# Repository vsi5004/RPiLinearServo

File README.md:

# RPiLinearServo

A closed-loop linear servo based on the RP2040, using a micro stepper linear actuator with an 8.5 mm throw and a BTT v1.3 TMC2209 driver. Designed as an RC servo replacement / turnout actuator for model railroads that allows for smooth and reliable slow speed operation and ease of configuration for a wide range of applications.

## Features

- Controllable via standard servo PWM signal allowing for plug-and-play integration in systems designed for miniature R/C servos
- Easy firmware updates - just drag and drop compiled binary into mounted drive to flash
- Widely configurable by editing a `CONFIG.INI` file when device is connected as a usb drive to allow for adaptation to wide range of use cases
- Smooth, quiet, controllable, and repeatable motion not available in smaller servos
- Non-backdrivable lead screw linear stage can be powered off in a low power state while not in use
- Automatic homing routine runs once and is then stored and persists throughout the life of the device
- Closed loop magnetic feedback allows for seamless, accurate adjustments if external factors cause motor to miss steps
- Interactive USB CLI (via serial monitor) exposes full command set for motion control, diagnostics, and debugging

## Hardware

| Component | Details |
|---|---|
| MCU | Waveshare RP2040-Zero |
| Driver | BTT TMC2209 v1.3 SilentStepStick |
| Actuator | Micro stepper linear slide, 8.4 mm travel (~208.3 full steps/mm) |
| Hall Sensor | TI DRV5055 A2 (optional, for closed-loop verification) |

See the [PCB README](PCB/README.md) for the full schematic, BOM, and GPIO assignments.

## Getting Started

### Flash the firmware

1. Hold **BOOTSEL** on the RP2040-Zero and plug in USB.
2. Drag `RPiLinearServo.uf2` onto the **RPI-RP2** drive.
3. The board reboots and enumerates as a composite USB device (CDC serial + MSC config drive).

Pre-built `.uf2` files are available on the [Releases](../../releases) page — or build from source (see the [Firmware README](Firmware/RPiLinearServo/README.md)).

### Connect a PWM signal

Wire a standard RC servo signal (1000–2000 µs) to GP0. On the first valid pulse the servo automatically homes (drives into the hardstop, backs off, and zeroes) then begins tracking the PWM target.

If the PWM signal is lost for more than 100 ms (configurable), the motor is disabled and the LED enters an idle heartbeat.

### Configure via USB drive

The device mounts a small USB drive named **LINEARSERVO** containing `CONFIG.INI`. Edit with any text editor, save, and **safely eject**. The firmware applies changes within ~500 ms.

```ini
[stroke]
stroke_mm = 8.40
full_steps_per_mm = 208.3

[driver]
dir_invert = false
run_current_ma = 100
hold_current_ma = 50

[motion]
default_speed_mm_s = 40.0
max_accel_mm_s2 = 80.0
auto_disable_ms = 2000

[rc_pwm]
min_us = 1000
max_us = 2000

[led]
dark_mode = false

[power]
sleep_when_idle = false

[sensor]
use_hall_effect = false
```

### USB CLI

Connect a serial terminal (PuTTY, minicom, `screen /dev/ttyACM0 115200`) to the CDC port. The CLI is always active alongside PWM control.

```
> help
Commands:
  move <steps> [speed_hz]  Move relative steps (negative = reverse)
  run [speed_hz]           Continuous stepping
  stop                     Stop immediately
  home                     Run homing sequence
  enable                   Enable motor driver
  disable                  Disable motor driver
  dir <fwd|rev>            Set direction for 'run'
  speed <hz>               Set default speed
  pos                      Print position
  status                   Print full status
  pwm                      Print PWM input status
  nvm                      Print/save position state
  hall                     Hall sensor reading
  hallcal                  Dump hall calibration table
  faultclr                 Clear stall fault
  help                     This message
```

CLI commands go through the same servo loop state machine as PWM-driven moves, so LED and driver enable behaviour is always consistent.

## Project Structure

| Directory | Description | Details |
|---|---|---|
| [Firmware/RPiLinearServo](Firmware/RPiLinearServo/README.md) | RP2040 firmware (C++17, Pico SDK) | Build instructions, architecture, module reference |
| [PCB](PCB/README.md) | KiCad 8 schematic & PCB | BOM, GPIO map, sourcing notes, Gerber outputs |
| [Mechanical](Mechanical/README.md) | 3D-printable mounting hardware | Mount variants, print settings, additional parts |
| [Docs](Docs/) | Renders and specifications | Project renders, design spec |

## License

This project is licensed under the [MIT License](LICENSE).

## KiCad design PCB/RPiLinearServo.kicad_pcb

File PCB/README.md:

# PCB — RPiLinearServo

KiCad schematic and PCB design files for the RPiLinearServo controller board.

## GPIO Assignments

| Signal | RP2040-Zero | TMC2209 Pin | Notes |
|---|---|---|---|
| PWM input | GP0 | — | RC servo signal via PIO1/SM1 |
| nENABLE | GP1 | EN | Active-low driver enable |
| STEP | GP2 | STEP | PIO0/SM0 driven |
| DIR | GP3 | DIR | GPIO |
| UART TX | GP4 | PDN/UART | Via 1 kΩ series resistor on PCB |
| UART RX | GP5 | PDN/UART | Loopback on bus |
| INDEX | GP7 | INDEX | Unused (reserved) |
| DIAG | GP9 | DIAG | Unused (reserved) |
| LED | GP16 | — | WS2812 RGB via PIO1/SM0 |
| Hall sensor | GP26 | — | DRV5055 A2 analog via ADC0 |

### UART bus isolation

The 1 kΩ series resistor (R1) between GP4 and the TMC2209 PDN/UART pin provides signal isolation so the driver can pull the bus low during reply frames without fighting the RP2040 TX output. GP4 is tri-stated after each write to allow the TMC2209 to respond over the half-duplex bus.

### PWM input protection

The PWM input on GP0 is routed through a 74LVC1G17 Schmitt-trigger buffer (U4) for signal conditioning. A TPD1E10B06DPYR ESD protection diode (D1) clamps the input to protect against transient voltage spikes from the RC servo signal line.

## Bill of Materials

| Ref | Part | Value / Description | Package | Qty |
|---|---|---|---|---|
| U2 | Waveshare RP2040-Zero | Dual-core RP2040 MCU module | Through-hole module | 1 |
| U1 | BTT TMC2209 v1.3 SilentStepStick | Stepper driver with UART | Through-hole module | 1 |
| U3 | TI DRV5055A2xDBZxQ1 | Ratiometric linear hall-effect sensor, 25 mV/mT | SOT-23 | 1 |
| U4 | 74LVC1G17 | Single Schmitt-trigger buffer | SOT-23-5 | 1 |
| D1 | TI TPD1E10B06DPYR | ESD protection diode, ±30 kV HBM | 0402 | 1 |
| C1, C3 | Panasonic EEEFPC101XAP | 100 µF 16 V aluminum electrolytic | Radial (custom footprint) | 2 |
| C2, C5 | Ceramic | 2.2 µF | 0805 | 2 |
| C4, C6 | Ceramic | 0.1 µF (decoupling) | 0402 | 2 |
| R1, R2 | Resistor | 1 kΩ | 0603 | 2 |
| R3 | Resistor | 330 Ω | 0603 | 1 |
| J1 | Pin header 1×3 | Hall sensor / PWM input connector | 2.54 mm pitch | 1 |
| J2 | Pin header 2×2 (omit, used for pads only)| Stepper motor phase connector | 2.54 mm pitch | 1 |

### Sourcing notes

| Part | Suggested source |
|---|---|
| Waveshare RP2040-Zero | [Waveshare](https://www.waveshare.com/rp2040-zero.htm), AliExpress, Amazon |
| BTT TMC2209 v1.3 SilentStepStick | [BIGTREETECH](https://biqu.equipment/products/bigtreetech-tmc2209-stepper-motor-driver-for-3d-printer-board-vs-tmc2208), Amazon, AliExpress |
| TI DRV5055A2xDBZxQ1 | DigiKey, Mouser, LCSC |
| 74LVC1G17 | DigiKey, Mouser, LCSC |
| TPD1E10B06DPYR | DigiKey (296-30406-1-ND), Mouser |
| Panasonic EEEFPC101XAP | DigiKey (PCE4534CT-ND), Mouser |
| Passives (0402/0603/0805) | LCSC, DigiKey, Mouser |

All SMD passives use hand-solder footprints with extended pads for easier assembly.

## Design Files

| Path | Description |
|---|---|
| `RPiLinearServo.kicad_sch` | Schematic |
| `RPiLinearServo.kicad_pcb` | PCB layout |
| `RPiLinearServo.kicad_pro` | KiCad project |
| `RPiLinearServo.step` | 3D model of assembled board |
| `Components/` | Custom KiCad symbol libraries + 3D STEP models |
| `CustomFootprints/` | Custom KiCad footprint libraries |

## Manufacturing Outputs

Pre-generated Gerber and drill files are in `Outputs/`:

| File | Description |
|---|---|
| `*-F_Cu.gbr`, `*-B_Cu.gbr` | Front/back copper |
| `*-F_Mask.gbr`, `*-B_Mask.gbr` | Front/back solder mask |
| `*-F_Paste.gbr`, `*-B_Paste.gbr` | Front/back paste stencil |
| `*-F_Silkscreen.gbr`, `*-B_Silkscreen.gbr` | Front/back silkscreen |
| `*-Edge_Cuts.gbr` | Board outline |
| `*-PTH.drl`, `*-NPTH.drl` | Plated / non-plated drill files |
| `*-top-pos.csv`, `*-bottom-pos.csv` | Pick-and-place position files |
| `*-BOM.csv` | Bill of materials (semicolon-delimited) |
| `*-job.gbrjob` | Gerber job file |

These files are ready to upload directly to PCB fabricators such as JLCPCB, PCBWay, or OSH Park.

### PCB specifications

| Parameter | Value |
|---|---|
| Minimum trace width | 0.2 mm |
| Default trace width | 0.2 mm |
| Via diameter / drill | 0.6 mm / 0.3 mm |
| Copper-to-edge clearance | 0.4 mm |
| Layers | 2 |

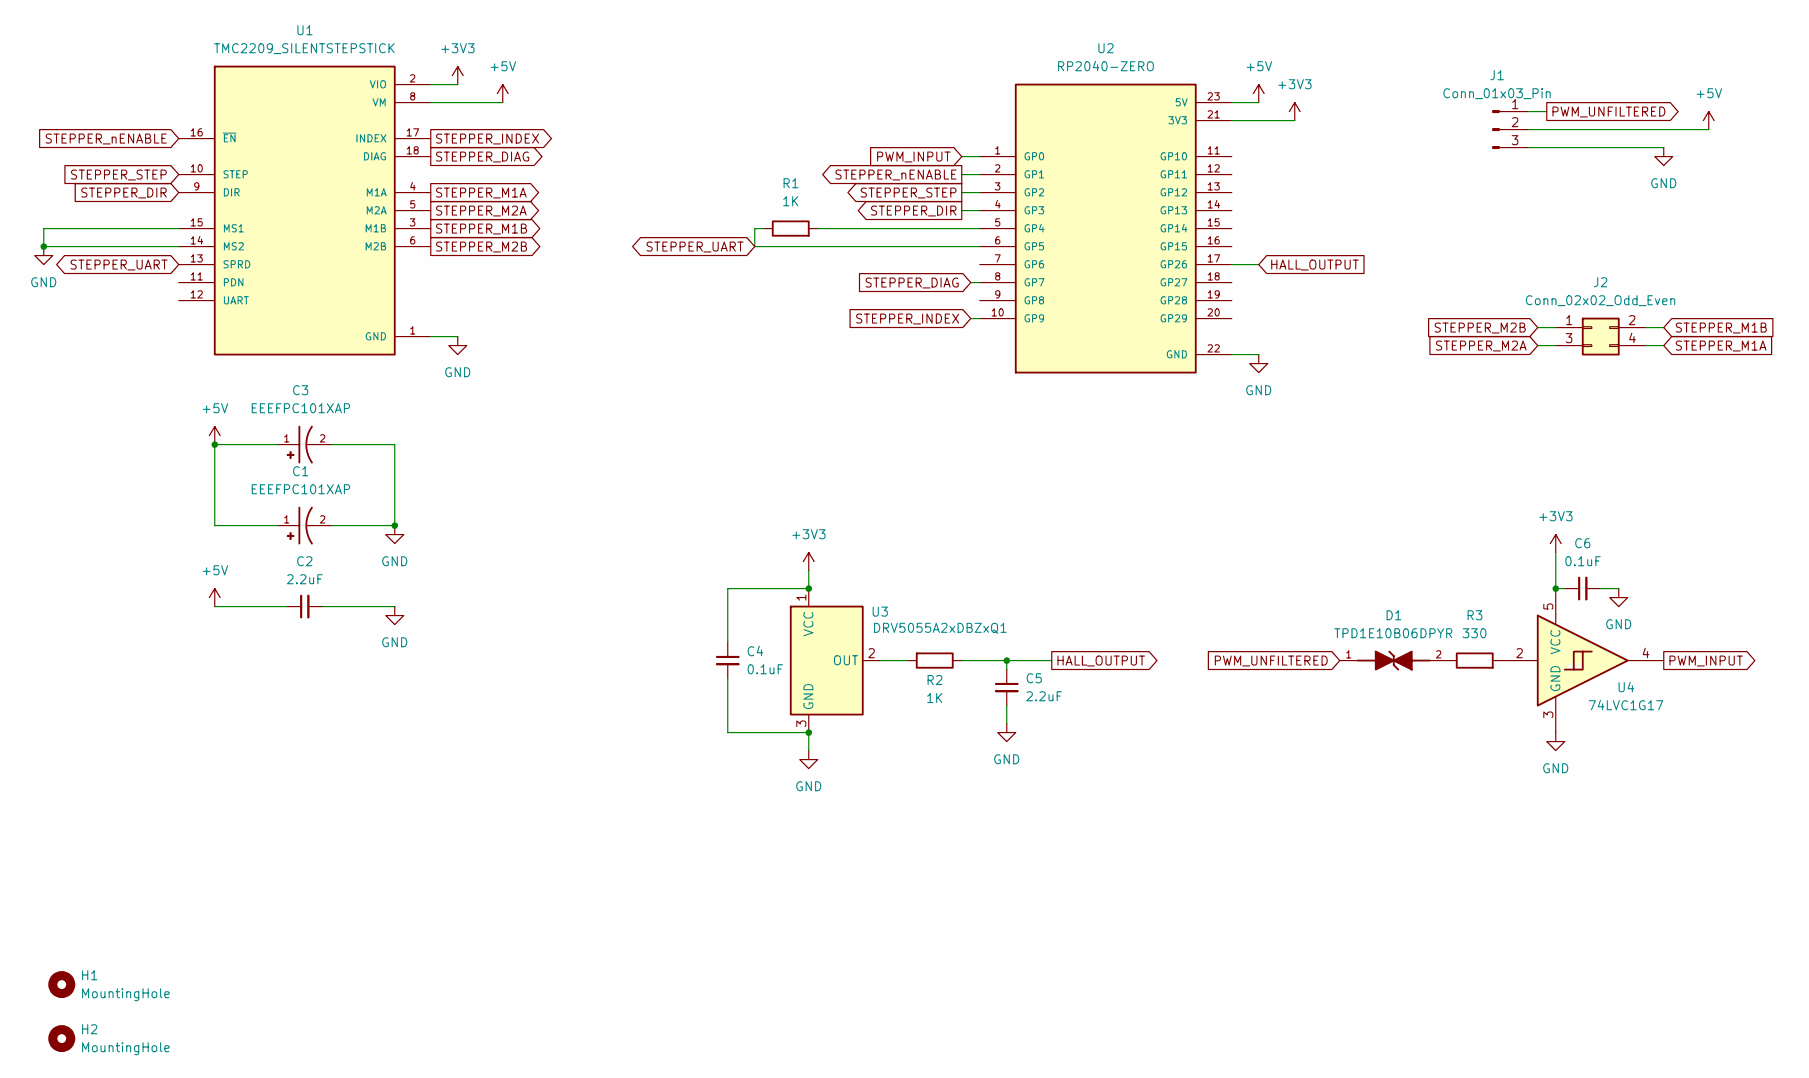
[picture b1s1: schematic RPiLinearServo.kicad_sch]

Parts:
C1, C3: EEEFPC101XAP; CAP_EEEFPC101XAP; PARTREV 10-Oct-19; DigiKey_Part_Number PCE4534CT-ND
C2, C5: 2.2uF; C_0805_2012Metric_Pad1.18x1.45mm_HandSolder
C4, C6: 0.1uF; C_0402_1005Metric_Pad0.74x0.62mm_HandSolder
D1: TPD1E10B06DPYR; D_0402_1005Metric_Pad0.77x0.64mm_HandSolder; PARTREV G; DigiKey_Part_Number 296-30406-1-ND
H1, H2: MountingHole; MountingHole_2.2mm_M2_DIN965_Pad
J1: Conn_01x03_Pin; PinHeader_1x03_P2.54mm_Vertical
J2: Conn_02x02_Odd_Even; PinHeader_2x02_P2.54mm_Vertical
R1, R2: 1K; R_0603_1608Metric_Pad0.98x0.95mm_HandSolder
R3: 330; R_0603_1608Metric_Pad0.98x0.95mm_HandSolder
U1: TMC2209_SILENTSTEPSTICK; MODULE_TMC2209_SILENTSTEPSTICK
U2: RP2040-ZERO; MODULE_RP2040-ZERO; PARTREV NA
U3: DRV5055A2xDBZxQ1; SOT-23_Handsoldering
U4: 74LVC1G17; SOT-23-5_HandSoldering

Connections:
+3V3: C4.1, C6.1, U1.2 (VIO), U2.21 (3V3), U3.1 (VCC), U4.5 (VCC)
+5V: C1.1, C2.1, C3.1, J1.2, U1.8 (VM), U2.23 (5V)
GND: C1.2, C2.2, C3.2, C4.2, C5.2, C6.2, J1.3, U1.1 (GND), U1.7 (GND), U1.14 (MS2), U1.15 (MS1), U2.22 (GND), U3.3 (GND), U4.3 (GND)
HALL_OUTPUT: C5.1, R2.1, U2.17 (GP26)
unnamed: D1.2, R3.1
unnamed: R3.2, U4.2
unnamed: R1.2, U2.5 (GP4)
unnamed: R2.2, U3.2 (OUT)
PWM_INPUT: U2.1 (GP0), U4.4
PWM_UNFILTERED: D1.1, J1.1
STEPPER_DIAG: U1.18 (DIAG), U2.8 (GP7)
STEPPER_DIR: U1.9 (DIR), U2.4 (GP3)
STEPPER_INDEX: U1.17 (INDEX), U2.10 (GP9)
STEPPER_M1A: J2.4, U1.4 (M1A)
STEPPER_M1B: J2.2, U1.3 (M1B)
STEPPER_M2A: J2.3, U1.5 (M2A)
STEPPER_M2B: J2.1, U1.6 (M2B)
STEPPER_STEP: U1.10 (STEP), U2.3 (GP2)
STEPPER_UART: R1.1, U1.13 (SPRD), U2.6 (GP5)
STEPPER_nENABLE: U1.16 (~EN), U2.2 (GP1)

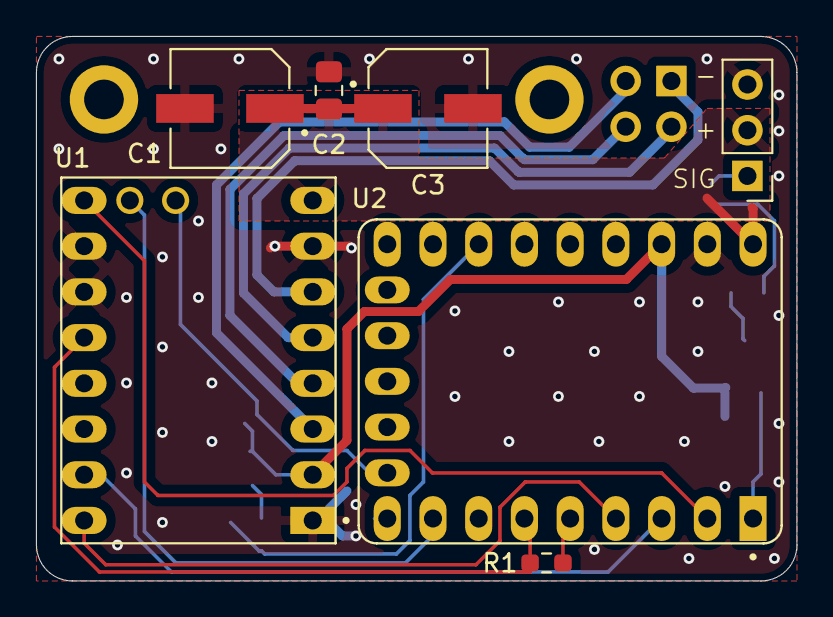
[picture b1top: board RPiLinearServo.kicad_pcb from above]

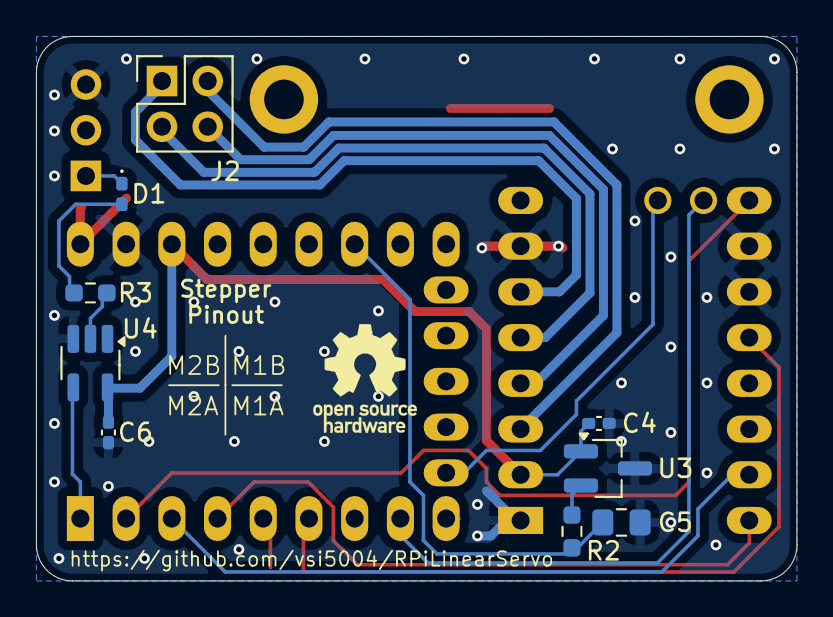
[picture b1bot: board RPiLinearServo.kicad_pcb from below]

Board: 2 copper layers, 42.2 x 30.2 mm, 18 parts (9 on the bottom side), 20 nets.

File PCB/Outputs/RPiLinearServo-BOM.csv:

"Id";"Designator";"Footprint";"Quantity";"Designation";"Supplier and ref";
1;"C1,C3";"CAP_EEEFPC101XAP";2;"EEEFPC101XAP";;;
2;"J1";"PinHeader_1x03_P2.54mm_Vertical";1;"Conn_01x03_Pin";;;
3;"U2";"MODULE_RP2040-ZERO";1;"RP2040-ZERO";;;
4;"R1,R2";"R_0603_1608Metric_Pad0.98x0.95mm_HandSolder";2;"1K";;;
5;"U1";"MODULE_TMC2209_SILENTSTEPSTICK";1;"TMC2209_SILENTSTEPSTICK";;;
6;"C2,C5";"C_0805_2012Metric_Pad1.18x1.45mm_HandSolder";2;"2.2uF";;;
7;"J2";"PinHeader_2x02_P2.54mm_Vertical";1;"Conn_02x02_Odd_Even";;;
8;"D1";"D_0402_1005Metric_Pad0.77x0.64mm_HandSolder";1;"TPD1E10B06DPYR";;;
9;"C4,C6";"C_0402_1005Metric_Pad0.74x0.62mm_HandSolder";2;"0.1uF";;;
10;"U4";"SOT-23-5_HandSoldering";1;"74LVC1G17";;;
11;"U3";"SOT-23_Handsoldering";1;"DRV5055A3xDBZxQ1";;;
12;"R3";"R_0603_1608Metric_Pad0.98x0.95mm_HandSolder";1;"330";;;

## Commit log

2026-03-08 Stage 1: PIO stepper, TMC2209 UART, hardstop homing, trapezoidal accel
    Firmware for RP2040-Zero + TMC2209 SilentStepStick linear servo:
    - PIO step pulse generation with IRQ-counted position tracking
    - Trapezoidal acceleration/deceleration via 1 kHz timer
    - TMC2209 single-wire UART config (current, microstepping, StealthChop)
    - Hardstop homing (110% stroke into end-stop, back off, zero)
    - WS2812 RGB status LED with breathing animation
2026-03-08 Stage 1+: PWM input, NVM persistence, LED idle heartbeat
    PWM input capture via PIO1/SM1 (16 ns resolution, 1000-2000 us range).
    Auto-home on first valid PWM pulse, continuous position tracking.
    PWM timeout disables motor and enters idle state.
    NVM dual-slot A/B flash storage with CRC32 validation and sequence
    counter. Homed flag and position restored on boot. Throttled saves
    (30 s min interval) to protect flash endurance.
2026-03-10 Add ESD protection on pwm input, fix wrapping bug in nvm storage logic
2026-03-10 Stage 2: USB MSC config drive with composite CDC+MSC
    - Composite USB device: CDC serial + MSC virtual FAT12 drive
    - CONFIG.INI on LINEARSERVO drive for runtime parameter editing
    - STATUS.TXT shows firmware version and last config apply result
    - INI parser with section/key matching, type validation, range checks
    - Flash-backed config persistence at 0x1F2000 (CRC32 validated)
    - 10 user-editable fields: stroke, direction, current, speed, accel,
2026-03-11 Refactor firmware, update PCB schematic, and add per-directory READMEs
    Firmware:
    - Add hall sensor driver, servo loop, hall verification, and position store
    - Move config/NVM storage to storage/ directory, add CRC32
    - Add status LED UI module, flash map header
    - Refactor stepgen, PWM input, TMC2209 driver, WS2812, homing, CLI
    - Add composite USB (CDC+MSC) with virtual FAT12 config drive
2026-03-11 Add dormant sleep, release pipeline, and MIT license
    Dormant sleep mode:
    - XOSC dormant with GPIO wake on GP0 rising edge (~13 mA)
    - Forced position save pre-sleep, RAM-based restore on wake
    - 5-second boot grace period for never-had-PWM entry path
    - Safe peripheral re-init (stepgen timer/IRQ teardown, USB stdio cleanup)
    - sleep_when_idle config field persisted in flash (CFG_VERSION 5)
2026-03-14 Refactor servo loop as explicit state machine, unify CLI/PWM API
    - Rewrite servo_loop.cpp as a 4-state machine (IDLE/HOMING/MOVING/HOLDING)
    with a single enter_state() controlling EN pin and LED
    - Add servo_loop_move/run/stop/enable/disable/home API; CLI commands now
    go through the same code path as PWM-driven moves
    - Fix LED stuck green after long PWM moves (MOVING -> IDLE when PWM already
    lost instead of lingering in HOLDING)
2026-03-17 Update Layout and BOM with minor routing and footprint changes for PWM input voltage protection
